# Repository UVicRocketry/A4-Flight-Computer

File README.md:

# Anduril 4 Flight Computer
**Project Charter:** [[[UVR-CH-068] Flight Computer Project Charter]](https://docs.google.com/document/d/1PksAvCCPt7eP-2tlsQyjIq21KkHghG1seeA3lu4UV-o/edit).

## Hardware
Hardware designed in KiCAD. If any footprints are added create a folder with the component name in the component-library folder and export all the files to there. When importing footprints and symbols add them to the A4-Flight-Computer library in KiCAD. Also add any datasheet and relevent documentation to this folder.

## Software
Software is an STM32CubeMX/STM32CubeIDE project using FreeRTOS.
[[Get STM32 software development tools]](https://www.st.com/en/development-tools/stm32-software-development-tools.html)

Unit testing: test infrastructure not set up yet.

### Source organization

The organizational idea is to separate the CubeMX-generated STM32 code from the project-specific application code:

```text
software/A4-Flight-Computer/
├── Core/                         # CubeMX-generated startup and HAL integration
│   ├── Inc/
│   └── Src/
├── App/                          # User-owned flight-computer application
|   ├── Inc/                      # Shared application headers such as config options
|   ├── Src/                      # General application sources such as initialization
│   ├── Services/                 # Services, state machines, etc. shared between tasks
│   ├── Tasks/                    # FreeRTOS task implementations
│   └── Interrupts/               # GPIO/timer/CAN interrupt handlers
├── Drivers/
│   ├── BSP/A4FlightComputer/     # Board-specific hardware abstraction
│   ├── CMSIS/
│   └── STM32H5xx_HAL_Driver/
└── Tests/
    ├── Unit/                     # Google Test unit tests
    └── Mocks/                    # Mock functions for use in unit tests
```

`Core/` should remain mostly as generated by CubeMX. Project-specific application code should be placed in `App/`, hardware interfaces specific to the A4 Flight Computer board
(i.e. accelerometer interface) should be placed in `Drivers/BSP/`, and Google Test cases and mocks should be placed in `Tests/Unit/` and `Tests/Mocks/`.

Handlers in `App/Interrupts/` shall be ISR-safe and perform minimal processing except setting/clearing flags and queuing data to be processed by Tasks. Hardware-independent logic
belongs in `App/Services/` and should not depend directly on STM32 HAL or FreeRTOS.

Unit tests are built on the host with Google Test. Application services
should be testable without STM32 hardware, HAL initialization, or starting the
FreeRTOS scheduler. Use interfaces and fakes for hardware-dependent behavior.

## Setup Guide
*[Fill out if applicable]*

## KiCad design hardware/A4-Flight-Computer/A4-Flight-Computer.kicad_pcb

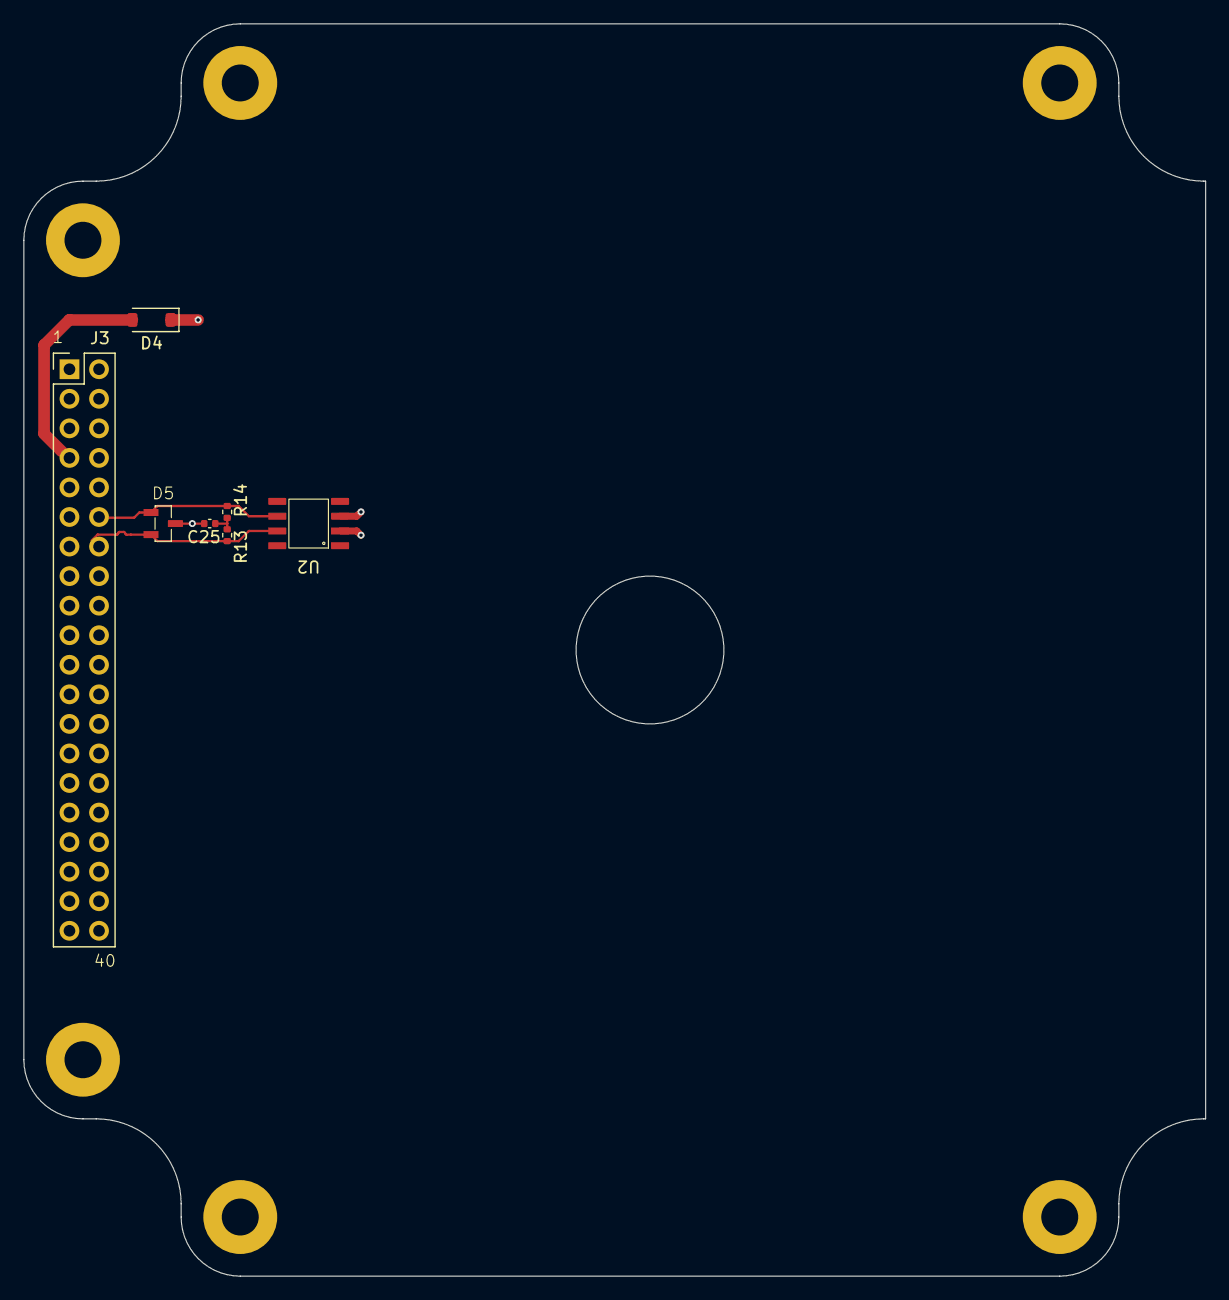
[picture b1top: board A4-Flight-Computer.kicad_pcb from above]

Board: 4 copper layers, 101.6 x 107.6 mm, 7 parts (0 on the bottom side), 6 nets.

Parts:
C25: 4.7nF; C_0402_1005Metric
D4: DSS14U; D_SOD-123
D5: ESD2CANFD24; ESD2CANFD24-SOT23
J3: LAB_Connector_02x20; LAB_PCB_With_Header
R13, R14: 60; R_0402_1005Metric
U2: TCAN3414; TCAN3414DR-SOIC8

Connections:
+3.3V: D4.1 (K), U2.3 (VCC)
/CAN+: D5.2 (IO2), J3.14 (CAN_H), R13.2, U2.7 (CANH)
/CAN-: D5.1 (IO1), J3.12 (CAN_L), R14.1, U2.6 (CANL)
GND: C25.2, D5.3 (GND), J3.2 (GND), J3.5 (GND), J3.10 (GND), J3.13 (GND), J3.18 (GND), J3.21 (GND), J3.26 (GND), J3.29 (GND), J3.34 (GND), J3.37 (GND), U2.2 (GND)
unnamed: C25.1, R13.1, R14.2
unnamed: D4.2 (A), J3.7 (3V3_FC)
